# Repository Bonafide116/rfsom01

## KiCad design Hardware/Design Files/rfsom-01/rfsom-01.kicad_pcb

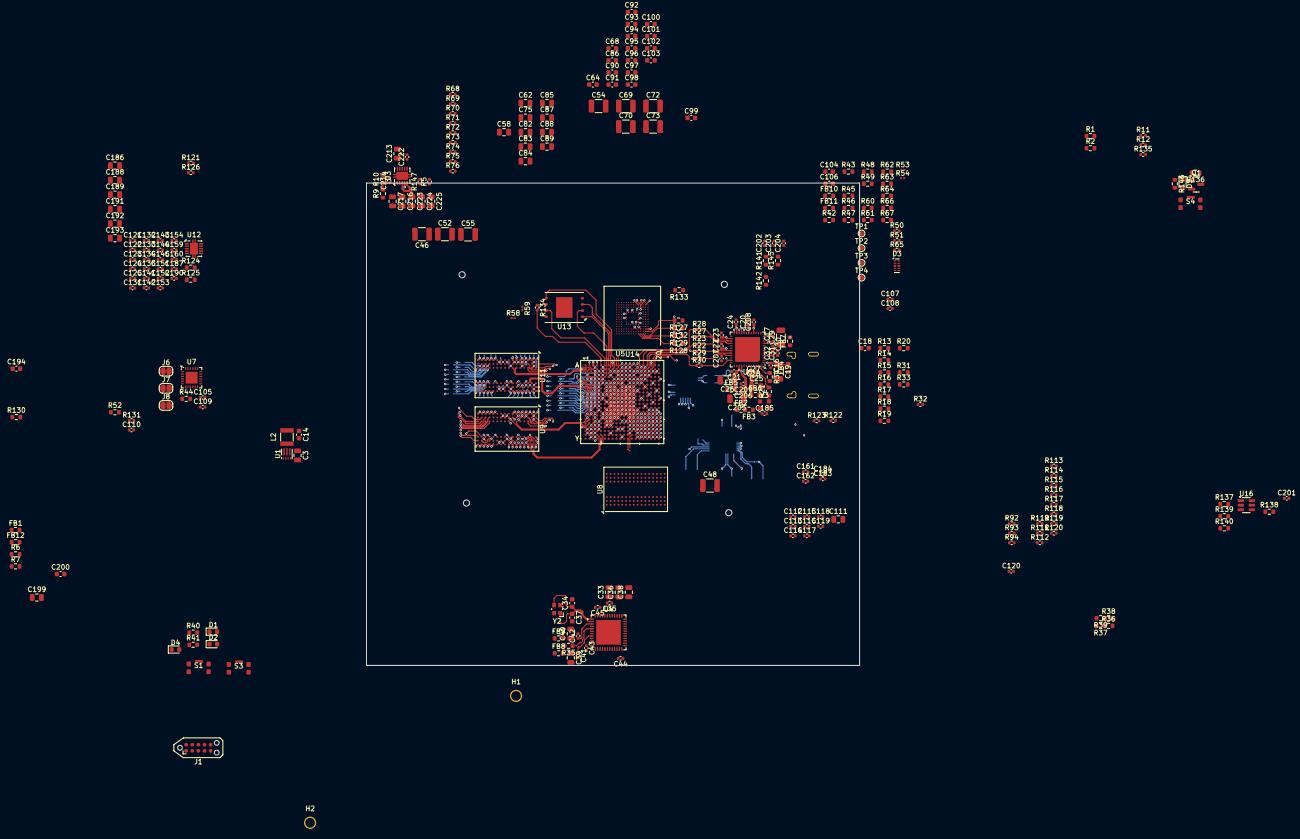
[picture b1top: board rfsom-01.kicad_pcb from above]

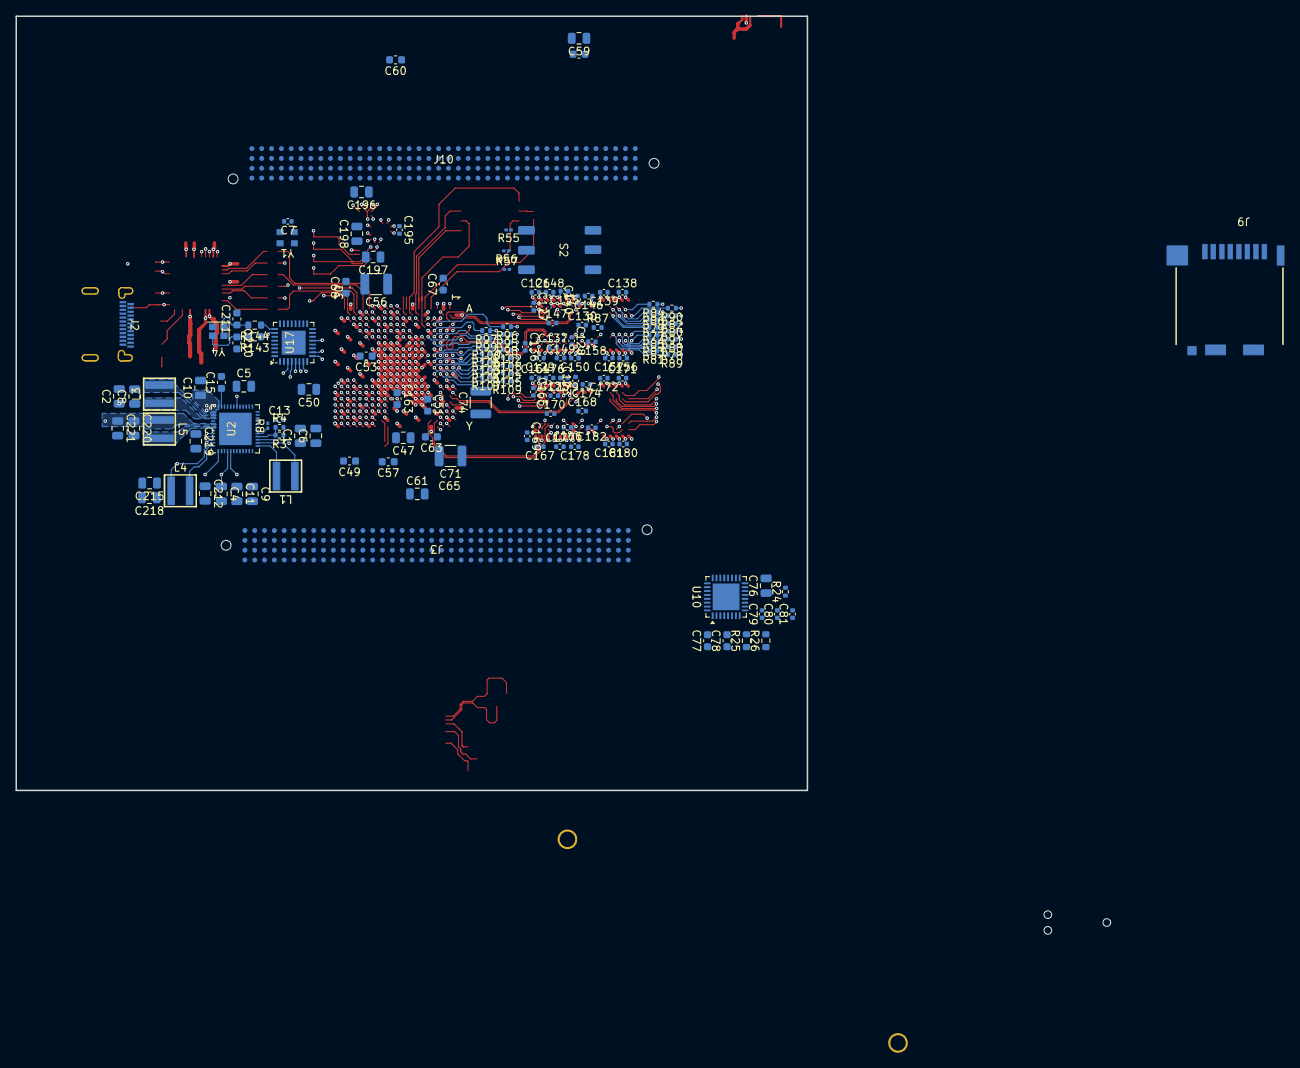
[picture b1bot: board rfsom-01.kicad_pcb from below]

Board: 10 copper layers, 102.2 x 100.0 mm, 432 parts (140 on the bottom side), 322 nets.

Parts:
C1, C8, C9, C10, C11, C47, C50, C58, C59, C61, C62, C75, C76, C82, C83, C84, C85, C87, C88, C89, C186, C212, C213, C218, C219, C221: CL21B475KPFNNNE; C_0805_2012Metric
C2, C4, C5, C6, C111, C188, C189, C191, C192, C193, C215, C216, C217, C220, C223, C224, C225: CL21B106KQQNFNE; C_0805_2012Metric
C3, C25, C33, C36, C38, C39, C40, C196, C197, C198, C199: CL21B475KAFNNNE; C_0805_2012Metric
C7, C13, C16, C17, C20, C21, C22, C23, C24, C27, C30, C31, C32, C35, C41, C42, C43, C44, C45, C79, C81, C105, C107, C108, C109, C110, C112, C113, C114, C115, C116, C117, C118, C119, C120, C185, C190, C195, C201, C202, C203, C204, C206, C207, C208, C209, C222: CL05B104KA5NNNC; C_0402_1005Metric
C14: GRM188R60G106ME47; C_0603_1608Metric
C15, C18, C77, C78, C104, C194, C200: CL10B105KA8NNNC; C_0603_1608Metric
C19, C26, C29, C205: CL31A106KBHNNNE; C_1206_3216Metric
C28, C80, C151, C160, C161, C162, C183, C184: CL05B103KB5NNNC; C_0402_1005Metric
C34, C37, C210, C211: CL10C060DB8NNNC; C_0603_1608Metric
C46, C48, C52, C55, C56, C73: GRM32EE70G107ME19K; C_1210_3225Metric
C49, C51, C53, C57, C60, C63, C64, C65, C66, C67, C68, C86, C90, C91, C92, C93, C94, C95, C96, C97, C98, C99, C100, C101, C102, C103, C106, C163: GRM188R70J474KA01D; C_0603_1608Metric
C54, C69, C70, C71, C72, C74: GRM32ER70J476ME20L; C_1210_3225Metric
C121, C122, C123, C124, C125, C126, C127, C128, C129, C130, C131, C132, C133, C134, C135, C136, C137, C138, C139, C140, C141, C142, C143, C144, C145, C146, C147, C148, C149, C150, C152, C153, C154, C155, C156, C157, C158, C159, C164, C165, C166, C167, C168, C169, C170, C171, C172, C173, C174, C175, C176, C177, C178, C179, C180, C181, C182: CL05B473KA5VPNC; C_0402_1005Metric
C187, C214: CL05B102KB5NNNC; C_0402_1005Metric
D1, D2, D4, D5: 150060BS75000; LED_0603_1608Metric
D3: ESD204DQAR; USON-10
FB1, FB2, FB3, FB4, FB5, FB6, FB7, FB8, FB9, FB10, FB11, FB12: MPZ1608S601ATA00; R_0603_1608Metric
H1, H2: MountingHole_Pad; MountingHole_2mm
J1: TC2050; Tag-Connect_TC2050-IDC-NL_2x05_P1.27mm_Vertical
J2: 2216100001
J3, J10: SEAM-40-02.0-L-04-2-A-K-TR; SEAM-40-XX.X-XXX-04-X-A-XX-XX
J6, J7, J8: SolderJumper-2_P1.3mm_Open_RoundedPad1.0x1.5mm
J9: DM3CS-SF
L1, L3, L4, L5: 74438357015; WE-MAPI
L2: DFE322512F-R47M=P2; IND_1210
Q1: BSS138; SOT-23
R1, R2, R9, R10, R13, R15, R17, R19, R25, R26, R63, R66, R67, R124, R125, R130, R133, R136, R137, R139, R140, R142: RC0603FR-0710KL; R_0603_1608Metric
R3: RC0402FR-13470KL; R_0402_1005Metric
R4, R5, R11, R12, R24, R126, R135, R147: RC0402FR-07100KL; R_0402_1005Metric
R6, R7: RC0603FR-135K11L; R_0603_1608Metric
R8, R53, R54, R55, R56, R57, R58, R59: RC0603FR-0720KL; R_0201_0603Metric
R14, R16, R18, R20, R31, R33, R60, R61, R62: RC0603FR-071KL; R_0603_1608Metric
R21: RC0603FR-0749R9L; R_0603_1608Metric
R22, R23, R27, R28, R29, R30, R95, R96, R97, R98, R99, R100, R101, R102, R103, R104, R105, R106, R107, R108, R109, R110, R111, R112, R113, R114, R115, R116, R117, R118, R131, R134: RC0402FR-0722RL; R_0402_1005Metric
R32, R50, R51, R92: RES_01; R_0402_1005Metric
R34: RC0603FR-076K04L; R_0603_1608Metric
R35: RES_01; R_0603_1608Metric
R36, R37, R38, R39, R42, R43: RC0603JR-070RL; R_0603_1608Metric
R40, R41, R49, R64, R146: RC0603FR-07220RL; R_0603_1608Metric
R44, R52, R127, R128, R129, R132: RC0603FR-0747K5L; R_0603_1608Metric
R45, R46, R47, R48, R143, R144: RC0402FR-07100RL; R_0603_1608Metric
R65, R68, R69, R70, R71, R72, R73, R74, R75, R76, R77, R78, R79, R80, R81, R82, R83, R84, R85, R86, R87, R88, R89, R90, R91, R93: RT0402FRE0740R2L; R_0402_1005Metric
R94, R119, R120: RC0402FR-0780R6L; R_0402_1005Metric
R121, R122, R123: RC0402FR-07240RL; R_0402_1005Metric
R138: RC0603FR-072KL; R_0603_1608Metric
R141: RC0603FR-078K06L; R_0603_1608Metric
R145: RC0603FR-071ML; R_0603_1608Metric
S1, S3, S4: 435441019830
S2: 219-3LPST
TP1, TP2, TP3, TP4: TestPoint_Pad_D1.0mm
U1: TPS62086RLT; RLT0007A
U2: TPS65218D0RSLT; RSL0048G
U3, U12: TPS51200DRCR; VSON-10-1EP_3x3mm_P0.5mm_EP1.65x2.4mm
U4: FT232HQ-REEL; QFN-48-1EP_7x7mm_P0.5mm_EP5.1x5.1mm
U5: XC7Z010-1CLG400C; CLG400
U6: KSZ9131RNXI-TR; MLPQ-48-1EP_7x7mm_P0.5mm
U7: TXS02612RTWR; QFN-24-1EP_4x4mm_P0.5mm
U8, U9, U11: AS4C256M16D3C-12BCN; BGA-96_9.0x13.0mm_Layout2x3x16_P0.8mm
U10: STM32L432KCUx; QFN-32-1EP_5x5mm_P0.5mm_EP3.45x3.45mm
U13: S25FL128SAGNFI003; PG-WSON-8_EP
U14: MX52LM04A11XSI; LFBGA-153_11.5x13mm_Layout14x14_P0.5mm
U16: 93LC56BT-I/OT; SOT-23-6
U17: USB3320C-EZK; QFN-32-1EP_5x5mm_P0.5mm
Y1: ECS-2033-500-BN; ECS-2033
Y2: ABM10-166-12.000MHZ-T3; Crystal_SMD_Abracon_ABM10-4Pin_2.5x2.0mm
Y3: ECS-2033-250-BN; ECS-2033
Y4: ECS-240-12-37B-CKY-TR; ECX-1637B

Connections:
+ETH_AVDDH: C16.1, C17.1, C19.1, FB4.2, U6.1 (AVDDH), U6.12 (AVDDH)
+ETH_AVDDL: C29.1, C30.1, C31.1, C32.1, FB7.1, U6.4 (AVDDL), U6.9 (AVDDL)
+ETH_DVDDH: C205.1, C206.1, C207.1, C208.1, C209.1, FB2.2, FB3.2, R33.2, U6.16 (DVDDH), U6.34 (DVDDH), U6.40 (DVDDH)
+ETH_DVDDL: C20.1, C21.1, C22.1, C23.1, C24.1, C26.1, FB5.2, U6.18 (DVDDL), U6.23 (DVDDL), U6.26 (DVDDL), U6.30 (DVDDL), U6.39 (DVDDL)
+LDO_3V3: C14.1, C76.1, C77.1, C78.1, C79.1, C80.1, C81.1, J1.1, L2.2, Q1.3 (D), R1.1, R2.1, R5.2, R11.1, R12.1, R25.1, R26.1, R135.1, R136.1, U1.3 (FB), U1.4 (VOS), U10.1 (VDD), U10.5 (VDDA), U10.17 (VDD)
+PL_VCC_1V5: C151.1, C188.1, C189.1, R124.1, U8.A1 (VDDQ), U8.A8 (VDDQ), U8.B2 (VDD), U8.C1 (VDDQ), U8.C9 (VDDQ), U8.D2 (VDDQ), U8.D9 (VDD), U8.E9 (VDDQ), U8.F1 (VDDQ), U8.G7 (VDD), U8.H2 (VDDQ), U8.H9 (VDDQ), U8.K2 (VDD), U8.K8 (VDD), U8.N1 (VDD), U8.N9 (VDD), U8.R1 (VDD), U8.R9 (VDD), U12.2 (VLDOIN)
+PL_VTT_0V75: C160.1, C191.1, C192.1, C193.1, U8.H1 (VREFDQ), U8.M8 (VREFCA), U12.3 (VO), U12.5 (VOSNS)
+PS_VCC_1V5: C216.1, C217.1, R9.1, R93.1, R120.2, U3.2 (VLDOIN)
+PS_VTT_0V75: C111.1, C112.1, C113.1, C114.1, C115.1, C116.1, C117.1, C118.1, C119.1, C120.1, C223.1, C224.1, C225.1, R68.1, R69.1, R70.1, R71.1, R72.1, R73.1, R74.1, R75.1, R76.1, R77.1, R78.1, R79.1, R80.1, R81.1, R82.1, R83.1, R84.1, R85.1, R86.1, R87.1, R88.1, R89.1, R90.1, R91.1, U3.3 (VO), U3.5 (VOSNS), U5.H6 (PS_DDR_VREF0_502), U5.P6 (PS_DDR_VREF1_502)
+PS_VTT_REF: C222.1, U3.6 (REFOUT), U12.6 (REFOUT)
+VCC_1V0: C48.1, C50.1, C53.1, C54.1, C58.1, C60.1, C64.1, C67.1, C73.1, C85.1, C90.1, C94.1, C215.1, C218.1, L4.1, U2.47 (FB1), U5.G7 (VCCPINT), U5.G11 (VCCBRAM), U5.G13 (VCCINT), U5.H10 (VCCBRAM), U5.H12 (VCCINT), U5.J7 (VCCPINT), U5.J13 (VCCINT), U5.K12 (VCCINT), U5.L7 (VCCPINT), U5.L13 (VCCINT), U5.M12 (VCCINT), U5.N7 (VCCPINT), U5.N13 (VCCINT), U5.P8 (VCCPINT), U5.P12 (VCCINT), U5.R7 (VCCPINT), U5.R13 (VCCINT)
+VCC_1V2: C220.1, C221.1, FB5.1, FB6.2, FB7.2, L5.1, U2.41 (FB2), U5.K10 (VREFN_0), U5.L9 (VREFP_0)
+VCC_1V5: C2.1, C8.1, C46.1, C47.1, C49.1, C51.1, C57.1, C63.1, C121.1, C122.1, C123.1, C124.1, C125.1, C126.1, C127.1, C128.1, C129.1, C130.1, C131.1, C132.1, C133.1, C134.1, C135.1, C136.1, C137.1, C138.1, C139.1, C140.1, C141.1, C142.1, C143.1, C144.1, C145.1, C146.1, C147.1, C148.1, C149.1, C150.1, C152.1, C153.1, C154.1, C155.1, C156.1, C157.1, C158.1, C159.1, C161.1, C164.1, C165.1, C166.1, C167.1, C168.1, C169.1, C170.1, C171.1, C172.1, C173.1, C174.1, C175.1, C176.1, C177.1, C178.1, C179.1, C180.1, C181.1, C182.1, C183.1, L3.1, U2.31 (IN_LS1), U2.39 (FB3), U5.A3 (VCCO_DDR_502), U5.D2 (VCCO_DDR_502), U5.E5 (VCCO_DDR_502), U5.G1 (VCCO_DDR_502), U5.H4 (VCCO_DDR_502), U5.L3 (VCCO_DDR_502), U5.P2 (VCCO_DDR_502), U5.R5 (VCCO_DDR_502), U5.U1 (VCCO_DDR_502), U5.V4 (VCCO_DDR_502), U9.A1 (VDDQ), U9.A8 (VDDQ), U9.B2 (VDD), U9.C1 (VDDQ), U9.C9 (VDDQ), U9.D2 (VDDQ), U9.D9 (VDD), U9.E9 (VDDQ), U9.F1 (VDDQ), U9.G7 (VDD), U9.H2 (VDDQ), U9.H9 (VDDQ), U9.K2 (VDD), U9.K8 (VDD), U9.N1 (VDD), U9.N9 (VDD), U9.R1 (VDD), U9.R9 (VDD), U11.A1 (VDDQ), U11.A8 (VDDQ), U11.B2 (VDD), U11.C1 (VDDQ), U11.C9 (VDDQ), U11.D2 (VDDQ), U11.D9 (VDD), U11.E9 (VDDQ), U11.F1 (VDDQ), U11.G7 (VDD), U11.H2 (VDDQ), U11.H9 (VDDQ), U11.K2 (VDD), U11.K8 (VDD), U11.N1 (VDD), U11.N9 (VDD), U11.R1 (VDD), U11.R9 (VDD)
+VCC_1V8: C4.1, C55.1, C56.1, C61.1, C62.1, C66.1, C68.1, C72.1, C84.1, C86.1, C104.1, C105.1, C163.1, C202.1, C203.1, C204.1, FB3.1, FB10.1, J6.2, R13.1, R15.1, R17.1, R19.1, R31.1, R52.1, R63.1, R66.1, R142.1, U2.4 (LDO1), U5.A13 (VCCO_MIO1_501), U5.B16 (VCCO_MIO1_501), U5.D12 (VCCO_MIO1_501), U5.E15 (VCCO_MIO1_501), U5.F8 (VCCPAUX), U5.G8 (VCCPLL), U5.G9 (VCCPAUX), U5.H8 (VCCPAUX), U5.J11 (VCCAUX), U5.K8 (VCCPAUX), U5.L11 (VCCAUX), U5.M8 (VCCPAUX), U5.N9 (VCCAUX), U5.N11 (VCCAUX), U5.P10 (VCCAUX), U5.R9 (VCCAUX), U7.5 (VCCA), U17.8 (REFSEL[0]), U17.11 (REFSEL[1]), U17.14 (REFSEL[2]), U17.28 (VDD18), U17.30 (VDD18), U17.32 (VDDIO)
+VCC_3V3: C1.1, C6.1, C7.1, C43.1, C44.1, C45.1, C52.1, C59.1, C65.1, C69.1, C70.1, C71.1, C74.1, C75.1, C82.1, C83.1, C87.1, C88.1, C89.1, C91.1, C92.1, C93.1, C95.1, C96.1, C97.1, C98.1, C99.1, C100.1, C101.1, C102.1, C103.1, C109.1, C110.1, C185.1, C186.1, C195.1, C196.1, C197.1, C198.1, C201.1, C213.1, D1.2 (A), D2.2 (A), FB2.1, FB4.1, FB8.1, FB9.1, J9.4 (VDD), R32.1, R50.2, R51.2, R53.1, R126.2, R127.1, R128.1, R129.1, R130.2, R132.1, R133.2, R137.1, R139.1, R140.1, R147.2, S2.4, S2.5, S2.6, U2.15 (DCDC4), U3.10 (VIN), U4.12 (VCCIO), U4.24 (VCCIO), U4.39 (VCCD), U4.46 (VCCIO), U5.B6 (VCCO_MIO0_500), U5.C19 (VCCO_35), U5.D7 (VCCO_MIO0_500), U5.F18 (VCCO_35), U5.H14 (VCCO_35), U5.J17 (VCCO_35), U5.K6 (VCCO_0), U5.K20 (VCCO_35), U5.M6 (CFGBVS_0), U5.M16 (VCCO_35), U5.N6 (RSVDVCC3), U5.N19 (VCCO_34), U5.R6 (RSVDVCC2), U5.R15 (VCCO_34), U5.T6 (RSVDVCC1), U5.T8 (VCCO_13), U5.T18 (VCCO_34), U5.U11 (VCCO_13), U5.V14 (VCCO_34), U5.W7 (VCCO_13), U5.W17 (VCCO_34), U5.Y10 (VCCO_13), U5.Y20 (VCCO_34), U7.17 (VCC_B1), U7.21 (VCC_B0), U12.10 (VIN), U13.8 (VCC), U14.C6 (VCCQ), U14.E6 (VCC), U14.F5 (VCC), U14.J10 (VCC), U14.K9 (VCC), U14.M4 (VCCQ), U14.N4 (VCCQ), U14.P3 (VCCQ), U14.P5 (VCCQ), U16.6 (VCC), U17.20 (VDD33), U17.21 (VBAT), Y1.1 (EN), Y1.4 (VDD), Y3.1 (EN), Y3.4 (VDD)
+VCC_DDR_1V5: C5.1, U2.30 (LS1)
+VIN_5V0: C3.1, C9.1, C10.1, C11.1, C33.1, C35.1, C212.1, C219.1, FB1.2, R3.1, U1.1 (EN), U1.7 (VIN), U2.1 (IN_DCDC1), U2.5 (IN_LDO1), U2.9 (AC_DET), U2.12 (IN_DCDC4), U2.27 (IN_BU), U2.36 (IN_BIAS), U2.37 (IN_DCDC3), U2.43 (IN_DCDC2), U4.40 (VREGIN)
+VTT_0V75: C162.1, C184.1, U9.H1 (VREFDQ), U9.M8 (VREFCA), U11.H1 (VREFDQ), U11.M8 (VREFCA)
+VUSB: C199.1, C200.1, FB1.1, J2.A4 (VBUS), J2.A9 (VBUS), J2.B4 (VBUS), J2.B9 (VBUS)
/TC_SWD_CLK: J1.5, U10.24 (PA14)
/TC_SWD_IO: J1.3, U10.23 (PA13)
/TC_USART_RX: J1.2, U10.8 (PA2)
/TC_USART_TX: J1.4, U10.25 (PA15)
/eth-phy/+ETH_1V2: C25.1, C27.1, C28.1, FB6.1, U6.44 (AVDDL_PLL)
/eth-phy/ENET0_MDC: U5.C10 (PS_MIO52_501), U6.36 (MDC)
/eth-phy/ENET0_RXCLK: R30.1, U5.B17 (PS_MIO22_501)
/eth-phy/ENET0_RXCLK_R: R30.2, U6.35 (RXC/PHYAD2)
/eth-phy/ENET0_RXCTL: R29.1, U5.D13 (PS_MIO27_501)
/eth-phy/ENET0_RXCTL_R: R29.2, U6.33 (RX_CTL/CLK125_EN)
/eth-phy/ENET0_RXD0: R22.1, U5.D11 (PS_MIO23_501)
/eth-phy/ENET0_RXD0_R: R13.2, R14.1, R22.2, U6.32 (RXD0/MODE0)
/eth-phy/ENET0_RXD1: R23.1, U5.A16 (PS_MIO24_501)
/eth-phy/ENET0_RXD1_R: R15.2, R16.1, R23.2, U6.31 (RXD1/MODE1)
/eth-phy/ENET0_RXD2: R27.1, U5.F15 (PS_MIO25_501)
/eth-phy/ENET0_RXD2_R: R17.2, R18.1, R27.2, U6.28 (RXD2/MODE2)
/eth-phy/ENET0_RXD3: R28.1, U5.A15 (PS_MIO26_501)
/eth-phy/ENET0_RXD3_R: R19.2, R20.1, R28.2, U6.27 (RXD3/MODE3)
/eth-phy/ENET0_TXCLK: U5.A19 (PS_MIO16_501), U6.24 (TXC)
/eth-phy/ENET0_TXCTL: U5.F14 (PS_MIO21_501), U6.25 (TX_CTL)
/eth-phy/ENET0_TXD0: U5.E14 (PS_MIO17_501), U6.19 (TXD0)
/eth-phy/ENET0_TXD1: U5.B18 (PS_MIO18_501), U6.20 (TXD1)
/eth-phy/ENET0_TXD2: U5.D10 (PS_MIO19_501), U6.21 (TXD2)
/eth-phy/ENET0_TXD3: U5.A17 (PS_MIO20_501), U6.22 (TXD3)
/eth-phy/ETH0_MDIO: R31.2, U5.C11 (PS_MIO53_501), U6.37 (MDIO)
/eth-phy/ETH_LED2: R33.1, U6.15 (LED2/PHYAD1)
/eth-phy/~ENET0_RST: C18.2, R32.2, U5.B13 (PS_MIO50_501), U6.42 (RESET_N)
/ftdi/FTDI_EECLK: R139.2, U4.44 (EECLK), U16.4 (CLK)
/ftdi/FTDI_EECS: R137.2, U4.45 (EECS), U16.5 (CS)
/ftdi/FTDI_EEDATA: R138.2, R140.2, U4.43 (EEDATA), U16.3 (DI)
/ftdi/FTDI_USB_D+: J2.A6 (D1+), J2.B6 (D2+), U4.6 (DM)
/ftdi/FTDI_USB_D-: J2.A7 (D1-), J2.B7 (D2-), U4.7 (DP)
/ftdi/RXLED: R40.1, U4.27 (ACBUS3)
/ftdi/TXLED: R41.1, U4.28 (ACBUS4)
/mcu/ST_I2C1_SCL: R2.2, R26.2, U2.3 (SCL), U10.29 (PB6)
/mcu/ST_I2C1_SDA: R1.2, R25.2, U2.2 (SDA), U10.30 (PB7)
/power/3V3_PGOOD: R5.1, U1.2 (PG)
/power/PMIC_PB: S4.2, S4.4, U2.44 (PB)
/power/PMIC_PGOOD: Q1.1 (G), R136.2, U2.8 (PGOOD)
/power/PMIC_nINT: R11.2, U2.45 (~INT)
/power/PMIC_nPFO: R135.2, U2.10 (~PFO)
/power/PMIC_nWKP: R12.2, U2.40 (~WAKEUP)
/power/PS_VTT_PGOOD: R147.1, U3.9 (PGOOD)
/soc/EMMC_CLK: R131.1, U5.D9 (PS_MIO12_500)
/soc/EMMC_CMD: R133.1, U5.C6 (PS_MIO11_500), U14.M5 (CMD)
/soc/EMMC_D0: R132.2, U5.E9 (PS_MIO10_500), U14.A3 (DAT0)
/soc/EMMC_D1: R129.2, U5.E8 (PS_MIO13_500), U14.A4 (DAT1)
/soc/EMMC_D2: R128.2, U5.C5 (PS_MIO14_500), U14.A5 (DAT2)
/soc/EMMC_D3: R127.2, U5.C8 (PS_MIO15_500), U14.B2 (DAT3)
/soc/FLSH_QSPI_IO0: R58.2, U5.B8 (PS_MIO2_500), U13.5 (SI/IO0)
/soc/FLSH_QSPI_IO1: R56.2, U5.D6 (PS_MIO3_500), U13.2 (SO/IO1)
/soc/FLSH_QSPI_IO2: R57.2, U5.B7 (PS_MIO4_500), U13.3 (~WP/IO2)
/soc/FLSH_QSPI_IO3: R55.2, U5.A6 (PS_MIO5_500), U13.7 (~HOLD/IO3)
/soc/FLSH_QSPI_SCK: R59.2, R134.2, U5.A5 (PS_MIO6_500)
/soc/FLSH_QSPI_nCS: U5.A7 (PS_MIO1_500), U13.1 (~CS)
/soc/SDC_CD: J7.2, J9.9 (CD), R52.2
/soc/SDC_CLK: J9.5 (CLK), U7.19 (CLK_B0)
/soc/SDC_CMD: J9.3 (CMD), U7.20 (CMD_B0)
/soc/SDC_DAT0: J9.7 (DAT0), U7.18 (DAT0_B0)
/soc/SDC_DAT1: J9.8 (DAT1), U7.16 (DAT1_B0)
/soc/SDC_DAT2: J9.1 (DAT2), U7.23 (DAT2_B0)
/soc/SDC_DAT3: J9.2 (DAT3), U7.22 (DAT3_B0)
/soc/SD_CLK: R65.2, U7.9 (CLKA)
/soc/SD_CMD: U5.C17 (PS_MIO41_501), U7.4 (CMDA)
/soc/SD_D0: U5.E12 (PS_MIO42_501), U7.6 (DAT0A)
/soc/SD_D1: U5.A9 (PS_MIO43_501), U7.7 (DAT1A)
/soc/SD_D2: U5.F13 (PS_MIO44_501), U7.1 (DAT2A)
/soc/SD_D3: U5.B15 (PS_MIO45_501), U7.3 (DAT3A)
/soc/SD_SEL: J6.1, R44.1, U7.24 (SEL)
/soc/soc-pl/DDR3_ADDR0: U5.P14 (IO_L6P_T0_34), U8.N3 (A0)
/soc/soc-pl/DDR3_ADDR1: U5.R14 (IO_L6N_T0_VREF_34), U8.P7 (A1)
/soc/soc-pl/DDR3_ADDR2: U5.Y16 (IO_L7P_T1_34), U8.P3 (A2)
/soc/soc-pl/DDR3_ADDR3: U5.Y17 (IO_L7N_T1_34), U8.N2 (A3)
/soc/soc-pl/DDR3_ADDR4: U5.W14 (IO_L8P_T1_34), U8.P8 (A4)
/soc/soc-pl/DDR3_ADDR5: U5.Y14 (IO_L8N_T1_34), U8.P2 (A5)
/soc/soc-pl/DDR3_ADDR6: U5.T16 (IO_L9P_T1_DQS_34), U8.R8 (A6)
/soc/soc-pl/DDR3_ADDR7: U5.U17 (IO_L9N_T1_DQS_34), U8.R2 (A7)
/soc/soc-pl/DDR3_ADDR8: U5.V15 (IO_L10P_T1_34), U8.T8 (A8)
/soc/soc-pl/DDR3_ADDR9: U5.W15 (IO_L10N_T1_34), U8.R3 (A9)
/soc/soc-pl/DDR3_ADDR10: U5.U14 (IO_L11P_T1_SRCC_34), U8.L7 (A10/AP)
/soc/soc-pl/DDR3_ADDR11: U5.U15 (IO_L11N_T1_SRCC_34), U8.R7 (A11)
/soc/soc-pl/DDR3_ADDR12: U5.U18 (IO_L12P_T1_MRCC_34), U8.N7 (A12/~BC)
/soc/soc-pl/DDR3_ADDR13: U5.U19 (IO_L12N_T1_MRCC_34), U8.T3 (A13)
/soc/soc-pl/DDR3_ADDR14: U5.N18 (IO_L13P_T2_MRCC_34), U8.T7 (A14)
/soc/soc-pl/DDR3_BA0: U5.U20 (IO_L15N_T2_DQS_34), U8.M2 (BA0)
/soc/soc-pl/DDR3_BA1: U5.N20 (IO_L14P_T2_SRCC_34), U8.N8 (BA1)
/soc/soc-pl/DDR3_BA2: U5.P20 (IO_L14N_T2_SRCC_34), U8.M3 (BA2)
/soc/soc-pl/DDR3_CK+: U5.V20 (IO_L16P_T2_34), U8.J7 (CK)
/soc/soc-pl/DDR3_CK-: U5.W20 (IO_L16N_T2_34), U8.K7 (~CK)
/soc/soc-pl/DDR3_CKE: U5.R16 (IO_L19P_T3_34), U8.K9 (CKE)
/soc/soc-pl/DDR3_D0: U5.R19 (IO_0_34), U8.E3 (DQ0)
/soc/soc-pl/DDR3_D1: U5.T11 (IO_L1P_T0_34), U8.F7 (DQ1)
/soc/soc-pl/DDR3_D2: U5.T10 (IO_L1N_T0_34), U8.F2 (DQ2)
/soc/soc-pl/DDR3_D3: U5.T12 (IO_L2P_T0_34), U8.F8 (DQ3)
/soc/soc-pl/DDR3_D4: U5.U12 (IO_L2N_T0_34), U8.H3 (DQ4)
/soc/soc-pl/DDR3_D5: U5.P19 (IO_L13N_T2_MRCC_34), U8.H8 (DQ5)
/soc/soc-pl/DDR3_D6: U5.T20 (IO_L15P_T2_DQS_34), U8.G2 (DQ6)
/soc/soc-pl/DDR3_D7: U5.R17 (IO_L19N_T3_VREF_34), U8.H7 (DQ7)
/soc/soc-pl/DDR3_D8: U5.V17 (IO_L21P_T3_DQS_34), U8.D7 (DQ8)
/soc/soc-pl/DDR3_D9: U5.V18 (IO_L21N_T3_DQS_34), U8.C3 (DQ9)
/soc/soc-pl/DDR3_D10: U5.W18 (IO_L22P_T3_34), U8.C8 (DQ10)
/soc/soc-pl/DDR3_D11: U5.W19 (IO_L22N_T3_34), U8.C2 (DQ11)
/soc/soc-pl/DDR3_D12: U5.N17 (IO_L23P_T3_34), U8.A7 (DQ12)
/soc/soc-pl/DDR3_D13: U5.P18 (IO_L23N_T3_34), U8.A2 (DQ13)
/soc/soc-pl/DDR3_D14: U5.P15 (IO_L24P_T3_34), U8.B8 (DQ14)
/soc/soc-pl/DDR3_D15: U5.P16 (IO_L24N_T3_34), U8.A3 (DQ15)
/soc/soc-pl/DDR3_DM0: U5.T14 (IO_L5P_T0_34), U8.E7 (LDM)
/soc/soc-pl/DDR3_DM1: U5.T15 (IO_L5N_T0_34), U8.D3 (UDM)
/soc/soc-pl/DDR3_DQS0+: U5.U13 (IO_L3P_T0_DQS_PUDC_B_34), U8.F3 (LDQS)
/soc/soc-pl/DDR3_DQS0-: U5.V13 (IO_L3N_T0_DQS_34), U8.G3 (~LDQS)
/soc/soc-pl/DDR3_DQS1+: U5.V12 (IO_L4P_T0_34), U8.C7 (UDQS)
/soc/soc-pl/DDR3_DQS1-: U5.W13 (IO_L4N_T0_34), U8.B7 (~UDQS)
/soc/soc-pl/DDR3_ODT0: U5.R18 (IO_L20N_T3_34), U8.K1 (ODT)
/soc/soc-pl/DDR3_nCAS: U5.Y19 (IO_L17N_T2_34), U8.K3 (~CAS)
/soc/soc-pl/DDR3_nCS: U5.T17 (IO_L20P_T3_34), U8.L2 (~CS)
/soc/soc-pl/DDR3_nRAS: U5.Y18 (IO_L17P_T2_34), U8.J3 (~RAS)
/soc/soc-pl/DDR3_nRST: U5.W16 (IO_L18N_T2_34), U8.T2 (~RESET)
/soc/soc-pl/DDR3_nWE: U5.V16 (IO_L18P_T2_34), U8.L3 (~WE)
/soc/soc-pl/ram-pl/PL_VTT_PGOOD: R126.1, U12.9 (PGOOD)
/soc/soc-ps/JTAG_TCK: D3.4 (IO3), D3.7 (NC), R47.1, TP3.1
/soc/soc-ps/JTAG_TCK_R: R36.2, R47.2, U5.F9 (TCK_0)
/soc/soc-ps/JTAG_TDI: D3.2 (IO2), D3.9 (NC), R46.1, TP2.1
/soc/soc-ps/JTAG_TDI_R: R38.2, R46.2, U5.G6 (TDI_0)
/soc/soc-ps/JTAG_TDO: D3.1 (IO1), D3.10 (NC), R45.1, TP1.1
/soc/soc-ps/JTAG_TDO_R: R45.2, U4.15 (ADBUS2), U5.F6 (TDO_0)
/soc/soc-ps/JTAG_TMS: D3.5 (IO4), D3.6 (NC), R48.1, TP4.1
/soc/soc-ps/JTAG_TMS_R: R48.2, U4.16 (ADBUS3), U5.J6 (TMS_0)
/soc/soc-ps/MIO7: R54.2, U5.D8 (PS_MIO7_500)
/soc/soc-ps/MIO8: R53.2, U5.D5 (PS_MIO8_500)
/soc/soc-ps/PS_CLK_50M: U5.E7 (PS_CLK_500), Y1.3 (OUT)
/soc/soc-ps/RGMII_VREF: R66.2, R67.1, U5.E11 (PS_MIO_VREF_501)
/soc/soc-ps/SD0_CD: J7.1, J8.2, U5.B12 (PS_MIO48_501)
/soc/soc-ps/USB0_CLK: R143.1, U5.A11 (PS_MIO36_501), U17.26 (REFCLK)
/soc/soc-ps/USB0_DATA0: U5.A14 (PS_MIO32_501), U17.3 (DATA[0])
/soc/soc-ps/USB0_DATA1: U5.D15 (PS_MIO33_501), U17.4 (DATA[1])
/soc/soc-ps/USB0_DATA2: U5.A12 (PS_MIO34_501), U17.5 (DATA[2])
/soc/soc-ps/USB0_DATA3: U5.F12 (PS_MIO35_501), U17.6 (DATA[3])
/soc/soc-ps/USB0_DATA4: U5.C16 (PS_MIO28_501), U17.7 (DATA[4])
/soc/soc-ps/USB0_DATA5: U5.A10 (PS_MIO37_501), U17.9 (DATA[5])
/soc/soc-ps/USB0_DATA6: U5.E13 (PS_MIO38_501), U17.10 (DATA[6])
/soc/soc-ps/USB0_DATA7: U5.C18 (PS_MIO39_501), U17.13 (DATA[7])
/soc/soc-ps/USB0_DIR: U5.C13 (PS_MIO29_501), U17.31 (DIR)
/soc/soc-ps/USB0_NXT: U5.E16 (PS_MIO31_501), U17.2 (NXT)
/soc/soc-ps/USB0_STP: U5.C15 (PS_MIO30_501), U17.29 (STP)
/soc/soc-ps/VADC+: C106.1, C107.1, C108.1, FB10.2, R42.2, U5.J9 (VCCADC_0), U5.K9 (VP_0)
/soc/soc-ps/VADC-: C106.2, C107.2, C108.2, FB11.2, R43.2, U5.J10 (GNDADC_0), U5.L10 (VN_0)
/soc/soc-ps/ZYNQ_DONE_0: D4.2 (A), U5.R11 (DONE_0)
/soc/soc-ps/ZYNQ_NRST: R63.2, R64.1, U5.B10 (PS_SRST_B_501)
/soc/soc-ps/~USB_RST: R142.2, U5.B9 (PS_MIO51_501), U17.27 (~RESET)
/soc/soc-ram/DDR3_A0: R109.2, U5.N2 (PS_DDR_A0_502)
/soc/soc-ram/DDR3_A1: R108.2, U5.K2 (PS_DDR_A1_502)
/soc/soc-ram/DDR3_A2: R107.2, U5.M3 (PS_DDR_A2_502)
/soc/soc-ram/DDR3_A3: R106.2, U5.K3 (PS_DDR_A3_502)
/soc/soc-ram/DDR3_A4: R105.2, U5.M4 (PS_DDR_A4_502)
/soc/soc-ram/DDR3_A5: R104.2, U5.L1 (PS_DDR_A5_502)
/soc/soc-ram/DDR3_A6: R103.2, U5.L4 (PS_DDR_A6_502)
/soc/soc-ram/DDR3_A7: R102.2, U5.K4 (PS_DDR_A7_502)
/soc/soc-ram/DDR3_A8: R101.2, U5.K1 (PS_DDR_A8_502)
/soc/soc-ram/DDR3_A9: R100.2, U5.J4 (PS_DDR_A9_502)
/soc/soc-ram/DDR3_A10: R99.2, U5.F5 (PS_DDR_A10_502)
/soc/soc-ram/DDR3_A11: R98.2, U5.G4 (PS_DDR_A11_502)
/soc/soc-ram/DDR3_A12: R97.2, U5.E4 (PS_DDR_A12_502)
/soc/soc-ram/DDR3_A13: R96.2, U5.D4 (PS_DDR_A13_502)
/soc/soc-ram/DDR3_A14: R95.2, U5.F4 (PS_DDR_A14_502)
/soc/soc-ram/DDR3_ADDR0: R77.2, R109.1, U9.N3 (A0), U11.N3 (A0)
/soc/soc-ram/DDR3_ADDR1: R78.2, R108.1, U9.P7 (A1), U11.P7 (A1)
/soc/soc-ram/DDR3_ADDR2: R79.2, R107.1, U9.P3 (A2), U11.P3 (A2)
/soc/soc-ram/DDR3_ADDR3: R80.2, R106.1, U9.N2 (A3), U11.N2 (A3)
/soc/soc-ram/DDR3_ADDR4: R81.2, R105.1, U9.P8 (A4), U11.P8 (A4)
/soc/soc-ram/DDR3_ADDR5: R82.2, R104.1, U9.P2 (A5), U11.P2 (A5)
/soc/soc-ram/DDR3_ADDR6: R83.2, R103.1, U9.R8 (A6), U11.R8 (A6)
/soc/soc-ram/DDR3_ADDR7: R84.2, R102.1, U9.R2 (A7), U11.R2 (A7)
/soc/soc-ram/DDR3_ADDR8: R85.2, R101.1, U9.T8 (A8), U11.T8 (A8)
/soc/soc-ram/DDR3_ADDR9: R86.2, R100.1, U9.R3 (A9), U11.R3 (A9)
/soc/soc-ram/DDR3_ADDR10: R87.2, R99.1, U9.L7 (A10/AP), U11.L7 (A10/AP)
/soc/soc-ram/DDR3_ADDR11: R88.2, R98.1, U9.R7 (A11), U11.R7 (A11)
/soc/soc-ram/DDR3_ADDR12: R89.2, R97.1, U9.N7 (A12/~BC), U11.N7 (A12/~BC)
/soc/soc-ram/DDR3_ADDR13: R90.2, R96.1, U9.T3 (A13), U11.T3 (A13)
/soc/soc-ram/DDR3_ADDR14: R91.2, R95.1, U9.T7 (A14), U11.T7 (A14)
/soc/soc-ram/DDR3_BA0: R76.2, R112.1, U9.M2 (BA0), U11.M2 (BA0)
/soc/soc-ram/DDR3_BA1: R75.2, R111.1, U9.N8 (BA1), U11.N8 (BA1)
/soc/soc-ram/DDR3_BA2: R74.2, R110.1, U9.M3 (BA2), U11.M3 (BA2)
/soc/soc-ram/DDR3_CK+: R119.1, U5.L2 (PS_DDR_CKP_502), U9.J7 (CK), U11.J7 (CK)
/soc/soc-ram/DDR3_CK-: R119.2, U5.M2 (PS_DDR_CKN_502), U9.K7 (~CK), U11.K7 (~CK)
/soc/soc-ram/DDR3_CKE: R73.2, R93.2, R117.1, U9.K9 (CKE), U11.K9 (CKE)
/soc/soc-ram/DDR3_D0: U5.B3 (PS_DDR_DQ1_502), U11.E3 (DQ0)
/soc/soc-ram/DDR3_D1: U5.D1 (PS_DDR_DQ5_502), U11.F7 (DQ1)
/soc/soc-ram/DDR3_D2: U5.A2 (PS_DDR_DQ2_502), U11.F2 (DQ2)
/soc/soc-ram/DDR3_D3: U5.E1 (PS_DDR_DQ7_502), U11.F8 (DQ3)
/soc/soc-ram/DDR3_D4: U5.C3 (PS_DDR_DQ0_502), U11.H3 (DQ4)
/soc/soc-ram/DDR3_D5: U5.C1 (PS_DDR_DQ6_502), U11.H8 (DQ5)
/soc/soc-ram/DDR3_D6: U5.A4 (PS_DDR_DQ3_502), U11.G2 (DQ6)
/soc/soc-ram/DDR3_D7: U5.D3 (PS_DDR_DQ4_502), U11.H7 (DQ7)
/soc/soc-ram/DDR3_D8: U5.H2 (PS_DDR_DQ13_502), U11.D7 (DQ8)
/soc/soc-ram/DDR3_D9: U5.H3 (PS_DDR_DQ11_502), U11.C3 (DQ9)
/soc/soc-ram/DDR3_D10: U5.J1 (PS_DDR_DQ15_502), U11.C8 (DQ10)
/soc/soc-ram/DDR3_D11: U5.G3 (PS_DDR_DQ10_502), U11.C2 (DQ11)
/soc/soc-ram/DDR3_D12: U5.J3 (PS_DDR_DQ12_502), U11.A7 (DQ12)
/soc/soc-ram/DDR3_D13: U5.E3 (PS_DDR_DQ9_502), U11.A2 (DQ13)
/soc/soc-ram/DDR3_D14: U5.H1 (PS_DDR_DQ14_502), U11.B8 (DQ14)
/soc/soc-ram/DDR3_D15: U5.E2 (PS_DDR_DQ8_502), U11.A3 (DQ15)
/soc/soc-ram/DDR3_D16: U5.R1 (PS_DDR_DQ19_502), U9.E3 (DQ0)
/soc/soc-ram/DDR3_D17: U5.U2 (PS_DDR_DQ22_502), U9.F7 (DQ1)
/soc/soc-ram/DDR3_D18: U5.P1 (PS_DDR_DQ16_502), U9.F2 (DQ2)
/soc/soc-ram/DDR3_D19: U5.U3 (PS_DDR_DQ23_502), U9.F8 (DQ3)
/soc/soc-ram/DDR3_D20: U5.P3 (PS_DDR_DQ17_502), U9.H3 (DQ4)
/soc/soc-ram/DDR3_D21: U5.U4 (PS_DDR_DQ21_502), U9.H8 (DQ5)
/soc/soc-ram/DDR3_D22: U5.R3 (PS_DDR_DQ18_502), U9.G2 (DQ6)
/soc/soc-ram/DDR3_D23: U5.T4 (PS_DDR_DQ20_502), U9.H7 (DQ7)
/soc/soc-ram/DDR3_D24: U5.Y3 (PS_DDR_DQ25_502), U9.D7 (DQ8)
/soc/soc-ram/DDR3_D25: U5.V3 (PS_DDR_DQ31_502), U9.C3 (DQ9)
/soc/soc-ram/DDR3_D26: U5.Y4 (PS_DDR_DQ27_502), U9.C8 (DQ10)
/soc/soc-ram/DDR3_D27: U5.W1 (PS_DDR_DQ26_502), U9.C2 (DQ11)
/soc/soc-ram/DDR3_D28: U5.W3 (PS_DDR_DQ29_502), U9.A7 (DQ12)
/soc/soc-ram/DDR3_D29: U5.V1 (PS_DDR_DQ24_502), U9.A2 (DQ13)
/soc/soc-ram/DDR3_D30: U5.Y2 (PS_DDR_DQ28_502), U9.B8 (DQ14)
/soc/soc-ram/DDR3_D31: U5.V2 (PS_DDR_DQ30_502), U9.A3 (DQ15)
/soc/soc-ram/DDR3_DM0: U5.A1 (PS_DDR_DM0_502), U11.E7 (LDM)
/soc/soc-ram/DDR3_DM1: U5.F1 (PS_DDR_DM1_502), U11.D3 (UDM)
/soc/soc-ram/DDR3_DM2: U5.T1 (PS_DDR_DM2_502), U9.E7 (LDM)
/soc/soc-ram/DDR3_DM3: U5.Y1 (PS_DDR_DM3_502), U9.D3 (UDM)
/soc/soc-ram/DDR3_DQS0+: U5.C2 (PS_DDR_DQS_P0_502), U11.F3 (LDQS)
/soc/soc-ram/DDR3_DQS0-: U5.B2 (PS_DDR_DQS_N0_502), U11.G3 (~LDQS)
/soc/soc-ram/DDR3_DQS1+: U5.G2 (PS_DDR_DQS_P1_502), U11.C7 (UDQS)
/soc/soc-ram/DDR3_DQS1-: U5.F2 (PS_DDR_DQS_N1_502), U11.B7 (~UDQS)
/soc/soc-ram/DDR3_DQS2+: U5.R2 (PS_DDR_DQS_P2_502), U9.F3 (LDQS)
/soc/soc-ram/DDR3_DQS2-: U5.T2 (PS_DDR_DQS_N2_502), U9.G3 (~LDQS)
/soc/soc-ram/DDR3_DQS3+: U5.W5 (PS_DDR_DQS_P3_502), U9.C7 (UDQS)
/soc/soc-ram/DDR3_DQS3-: U5.W4 (PS_DDR_DQS_N3_502), U9.B7 (~UDQS)
/soc/soc-ram/DDR3_ODT0: R68.2, R118.1, U9.K1 (ODT), U11.K1 (ODT)
/soc/soc-ram/DDR3_RST: R92.1, U5.B4 (PS_DDR_DRST_B_502)
/soc/soc-ram/DDR3_nCAS: R70.2, R114.1, U9.K3 (~CAS), U11.K3 (~CAS)
/soc/soc-ram/DDR3_nCS: R72.2, R115.1, U9.L2 (~CS), U11.L2 (~CS)
/soc/soc-ram/DDR3_nRAS: R71.2, R113.1, U9.J3 (~RAS), U11.J3 (~RAS)
/soc/soc-ram/DDR3_nRST: U9.T2 (~RESET), U11.T2 (~RESET)
/soc/soc-ram/DDR3_nWE: R69.2, R116.1, U9.L3 (~WE), U11.L3 (~WE)
/soc/~EMMC_RST: R130.1, U14.K5 (~RST)
/~TC_SWD_RST: J1.7, R24.1, U10.4 (NRST)
GND: C1.2, C2.2, C3.2, C4.2, C5.2, C6.2, C7.2, C8.2, C9.2, C10.2, C11.2, C13.2, C14.2, C15.2, C16.2, C17.2, C18.1, C19.2, C20.2, C21.2, C22.2, C23.2, C24.2, C25.2, C26.2, C27.2, C28.2, C29.2, C30.2, C31.2, C32.2, C33.2, C34.2, C35.2, C36.2, C37.2, C38.2, C39.2, C40.2, C41.2, C42.2, C43.2, C44.2, C45.2, C46.2, C47.2, C48.2, C49.2, C50.2, C51.2, C52.2, C53.2, C54.2, C55.2, C56.2, C57.2, C58.2, C59.2, C60.2, C61.2, C62.2, C63.2, C64.2, C65.2, C66.2, C67.2, C68.2, C69.2, C70.2, C71.2, C72.2, C73.2, C74.2, C75.2, C76.2, C77.2, C78.2, C79.2, C80.2, C81.2, C82.2, C83.2, C84.2, C85.2, C86.2, C87.2, C88.2, C89.2, C90.2, C91.2, C92.2, C93.2, C94.2, C95.2, C96.2, C97.2, C98.2, C99.2, C100.2, C101.2, C102.2, C103.2, C104.2, C105.2, C109.2, C110.2, C111.2, C112.2, C113.2, C114.2, C115.2, C116.2, C117.2, C118.2, C119.2, C120.2, C121.2, C122.2, C123.2, C124.2, C125.2, C126.2, C127.2, C128.2, C129.2, C130.2, C131.2, C132.2, C133.2, C134.2, C135.2, C136.2, C137.2, C138.2, C139.2, C140.2, C141.2, C142.2, C143.2, C144.2, C145.2, C146.2, C147.2, C148.2, C149.2, C150.2, C151.2, C152.2, C153.2, C154.2, C155.2, C156.2, C157.2, C158.2, C159.2, C160.2, C161.2, C162.2, C163.2, C164.2, C165.2, C166.2, C167.2, C168.2, C169.2, C170.2, C171.2, C172.2, C173.2, C174.2, C175.2, C176.2, C177.2, C178.2, C179.2, C180.2, C181.2, C182.2, C183.2, C184.2, C185.2, C186.2, C187.2, C188.2, C189.2, C190.2, C191.2, C192.2, C193.2, C194.2, C195.2, C196.2, C197.2, C198.2, C201.2, C202.2, C203.2, C204.2, C205.2, C206.2, C207.2, C208.2, C209.2, C210.2, C211.2, C212.2, C213.2, C214.2, C215.2, C216.2, C217.2, C218.2, C219.2, C220.2, C221.2, C222.2, C223.2, C224.2, C225.2, D3.3 (GND), D3.8 (GND), FB11.1, FB12.2, H1.1, H2.1, J1.9, J9.6 (VSS), J9.S1, J9.S2, J9.S3, J9.S4, R4.2, R8.2, R10.2, R14.2, R16.2, R18.2, R20.2, R24.2, R34.2, R35.2, R44.2, R49.1, R54.1, R58.1, R59.1, R60.2, R61.2, R62.2, R67.2, R92.2, R94.2, R121.2, R122.2, R123.2, R125.2, R141.2, R146.2, S1.2, S1.4, S3.2, S3.4, S4.1, S4.3, U1.5 (GND), U2.20 (L5), U2.21 (FB5), U2.22 (FB6), U2.23 (L6), U2.24 (SYS_BU), U2.49 (EP), U3.4 (PGND), U3.8 (GND), U3.11 (EP), U4.4 (AGND), U4.9 (AGND), U4.10 (GND), U4.11 (GND), U4.22 (GND), U4.23 (GND), U4.35 (GND), U4.36 (GND), U4.41 (AGND), U4.42 (TEST), U4.47 (GND), U4.48 (GND), U5.A8 (GND), U5.A18 (GND), U5.B1 (GND), U5.B11 (GND), U5.C4 (GND), U5.C9 (GND), U5.C14 (GND), U5.D17 (GND), U5.E10 (GND), U5.E20 (GND), U5.F3 (GND), U5.F7 (GND), U5.F10 (RSVDGND), U5.G10 (GND), U5.G12 (GND), U5.G16 (GND), U5.H7 (GND), U5.H9 (GND), U5.H11 (GND), U5.H13 (GND), U5.H19 (GND), U5.J2 (GND), U5.J8 (GND), U5.J12 (GND), U5.K5 (GND), U5.K7 (GND), U5.K11 (GND), U5.K13 (GND), U5.K15 (GND), U5.L8 (GND), U5.L12 (GND), U5.L18 (GND), U5.M1 (GND), U5.M7 (GND), U5.M9 (DXP_0), U5.M10 (DXN_0), U5.M11 (GND), U5.M13 (GND), U5.N4 (GND), U5.N8 (GND), U5.N10 (GND), U5.N12 (GND), U5.N14 (GND), U5.P7 (GND), U5.P9 (GND), U5.P11 (GND), U5.P13 (GND), U5.P17 (GND), U5.R8 (GND), U5.R12 (GND), U5.R20 (GND), U5.T3 (GND), U5.T7 (GND), U5.T13 (GND), U5.U6 (GND), U5.U16 (GND), U5.V9 (GND), U5.V19 (GND), U5.W2 (GND), U5.W12 (GND), U5.Y5 (GND), U5.Y15 (GND), U6.29 (VSS), U6.45 (XO), U6.49 (EP), U7.2 (GND), U7.11 (GND), U7.25 (EP), U8.A9 (VSS), U8.B1 (VSSQ), U8.B3 (VSS), U8.B9 (VSSQ), U8.D1 (VSSQ), U8.D8 (VSSQ), U8.E1 (VSS), U8.E2 (VSSQ), U8.E8 (VSSQ), U8.F9 (VSSQ), U8.G1 (VSSQ), U8.G8 (VSS), U8.G9 (VSSQ), U8.J2 (VSS), U8.J8 (VSS), U8.M1 (VSS), U8.M9 (VSS), U8.P1 (VSS), U8.P9 (VSS), U8.T1 (VSS), U8.T9 (VSS), U9.A9 (VSS), U9.B1 (VSSQ), U9.B3 (VSS), U9.B9 (VSSQ), U9.D1 (VSSQ), U9.D8 (VSSQ), U9.E1 (VSS), U9.E2 (VSSQ), U9.E8 (VSSQ), U9.F9 (VSSQ), U9.G1 (VSSQ), U9.G8 (VSS), U9.G9 (VSSQ), U9.J2 (VSS), U9.J8 (VSS), U9.M1 (VSS), U9.M9 (VSS), U9.P1 (VSS), U9.P9 (VSS), U9.T1 (VSS), U9.T9 (VSS), U10.16 (VSS), U10.32 (VSS), U10.33 (VSS), U11.A9 (VSS), U11.B1 (VSSQ), U11.B3 (VSS), U11.B9 (VSSQ), U11.D1 (VSSQ), U11.D8 (VSSQ), U11.E1 (VSS), U11.E2 (VSSQ), U11.E8 (VSSQ), U11.F9 (VSSQ), U11.G1 (VSSQ), U11.G8 (VSS), U11.G9 (VSSQ), U11.J2 (VSS), U11.J8 (VSS), U11.M1 (VSS), U11.M9 (VSS), U11.P1 (VSS), U11.P9 (VSS), U11.T1 (VSS), U11.T9 (VSS), U12.4 (PGND), U12.8 (GND), U12.11 (EP), U13.4 (VSS), U13.9 (EP), U14.A6 (VSS), U14.C4 (VSSQ), U14.E7 (VSS), U14.G5 (VSS), U14.H10 (VSS), U14.J5 (VSS), U14.K8 (VSS), U14.N2 (VSSQ), U14.N5 (VCCQ), U14.P4 (VSSQ), U14.P6 (VSSQ), U16.2 (VSS), Y1.2 (GND), Y2.2, Y2.4, Y3.2 (GND), Y4.2, Y4.4
GND_USB: C199.2, C200.2, FB12.1, J2.A1 (GND), J2.A12 (GND), J2.B1 (GND), J2.B12 (GND), J2.SH1 (SHIELD1), J2.SH2 (SHIELD2), R6.2, R7.2
unnamed: C210.1, R143.2, R145.1, Y4.3
unnamed: C211.1, R144.2, R145.2, Y4.1
unnamed: D1.1 (K), R40.2
unnamed: D2.1 (K), R41.2
unnamed: D4.1 (K), R49.2
unnamed: D5.2 (A), Q1.2 (S)
unnamed: D5.1 (K), R146.1
unnamed: J2.A5 (CC1), R6.1
unnamed: J2.B5 (CC2), R7.1
unnamed: R55.1, R60.1, S2.1
unnamed: R56.1, R61.1, S2.2
unnamed: R57.1, R62.1, S2.3
unnamed: R64.2, S3.1, S3.3
unnamed: L2.1, U1.6 (SW)
unnamed: R8.1, U2.17 (DC34_SEL)
unnamed: C15.1, U2.35 (INT_LDO)
unnamed: L4.2, U2.48 (L1)
unnamed: L5.2, U2.42 (L2)
unnamed: L3.2, U2.38 (L3)
unnamed: L1.2, U2.13 (L4A)
unnamed: L1.1, U2.14 (L4B)
unnamed: C13.1, R3.2, R4.1, U2.16 (PFI)
unnamed: C214.1, R9.2, R10.1, U3.1 (REFIN)
unnamed: R36.1, R37.1, U4.13 (ADBUS0)
unnamed: R38.1, R39.1, U4.14 (ADBUS1)
unnamed: R35.1, U4.5 (REF)
unnamed: C38.1, U4.37 (VCCA)
unnamed: C36.1, U4.38 (VCCCORE)
unnamed: C40.1, C42.1, FB9.2, U4.3 (VPHY)
unnamed: C39.1, C41.1, FB8.2, U4.8 (VPLL)
unnamed: C34.1, U4.1 (XCSI), Y2.3
unnamed: C37.1, U4.2 (XCSO), Y2.1
unnamed: R51.1, U5.R10 (INIT_B_0)
unnamed: R50.1, S1.1, S1.3, U5.L6 (PROGRAM_B_0)
unnamed: R65.1, U5.D14 (PS_MIO40_501)
unnamed: R112.2, U5.L5 (PS_DDR_BA0_502)
unnamed: R111.2, U5.R4 (PS_DDR_BA1_502)
unnamed: R110.2, U5.J5 (PS_DDR_BA2_502)
unnamed: R114.2, U5.P5 (PS_DDR_CAS_B_502)
unnamed: R117.2, U5.N3 (PS_DDR_CKE_502)
unnamed: R115.2, U5.N1 (PS_DDR_CS_B_502)
unnamed: R113.2, U5.P4 (PS_DDR_RAS_B_502)
unnamed: R116.2, U5.M5 (PS_DDR_WE_B_502)
unnamed: R34.1, U6.48 (ISET)
unnamed: R21.2, U6.46 (XI)
unnamed: R121.1, U8.L8 (ZQ)
unnamed: R123.1, U9.L8 (ZQ)
unnamed: R122.1, U11.L8 (ZQ)
unnamed: C187.1, R124.2, R125.1, U12.1 (REFIN)
unnamed: R134.1, U13.6 (SCK)
unnamed: R131.2, U14.M6 (CLK)
unnamed: U14.A11 (DVDD), U14.G14 (DVDD), U14.M2 (DVDD), U14.P11 (DVDD)
unnamed: U14.A8 (DVDDQ), U14.B13 (DVDDQ), U14.C14 (DVDDQ), U14.G3 (DVDDQ), U14.G13 (DVDDQ), U14.H1 (DVDDQ), U14.H13 (DVDDQ), U14.M14 (DVDDQ), U14.N13 (DVDDQ), U14.P7 (DVDDQ), U14.P8 (DVDDQ)
unnamed: U14.A10 (DVSS), U14.C1 (DVSS), U14.H14 (DVSS), U14.K2 (DVSS), U14.M1 (DVSS)
unnamed: U14.A9 (DVSSQ), U14.A12 (DVSSQ), U14.D14 (DVSSQ), U14.F14 (DVSSQ), U14.L14 (DVSSQ), U14.N6 (DVSSQ), U14.P9 (DVSSQ), U14.P12 (DVSSQ)
unnamed: U14.A1 (NC), U14.A2 (NC), U14.A13 (NC), U14.A14 (NC), U14.B1 (NC), U14.B7 (NC), U14.B8 (NC), U14.B9 (NC), U14.B10 (NC), U14.B11 (NC), U14.B12 (NC), U14.B14 (NC), U14.C3 (NC), U14.C5 (NC), U14.C7 (NC), U14.C8 (NC), U14.C9 (NC), U14.C10 (NC), U14.C11 (NC), U14.C12 (NC), U14.C13 (NC), U14.D1 (NC), U14.D2 (NC), U14.D3 (NC), U14.D4 (NC), U14.D12 (NC), U14.D13 (NC), U14.E1 (NC), U14.E2 (NC), U14.E3 (NC), U14.E12 (NC), U14.E13 (NC), U14.E14 (NC), U14.F2 (NC), U14.F3 (NC), U14.F12 (NC), U14.F13 (NC), U14.G1 (NC), U14.G2 (NC), U14.G12 (NC), U14.H2 (NC), U14.H3 (NC), U14.H12 (NC), U14.J1 (NC), U14.J2 (NC), U14.J3 (NC), U14.J12 (NC), U14.J13 (NC), U14.K1 (NC), U14.K3 (NC), U14.K12 (NC), U14.K13 (NC), U14.K14 (NC), U14.L1 (NC), U14.L2 (NC), U14.L3 (NC), U14.L12 (NC), U14.L13 (NC), U14.M3 (NC), U14.M7 (NC), U14.M8 (NC), U14.M9 (NC), U14.M10 (NC), U14.M11 (NC), U14.M12 (NC), U14.M13 (NC), U14.N1 (NC), U14.N3 (NC), U14.N7 (NC), U14.N8 (NC), U14.N9 (NC), U14.N11 (NC), U14.N12 (NC), U14.N14 (NC), U14.P1 (NC), U14.P2 (NC), U14.P13 (NC), U14.P14 (NC)
unnamed: U14.A7 (RFU), U14.E5 (RFU), U14.K6 (RFU), U14.K7 (RFU)
unnamed: C194.1, U14.C2 (VDDI)
unnamed: U14.E8 (VSF), U14.E9 (VSF), U14.E10 (VSF), U14.F10 (VSF), U14.G10 (VSF), U14.K10 (VSF), U14.P10 (VSF)
unnamed: R138.1, U16.1 (DO)
unnamed: R141.1, U17.24 (RBIAS)
unnamed: R144.1, U17.25 (XO)
unnamed: R21.1, Y3.3 (OUT)

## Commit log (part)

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2025-05-31 initial commit; significant progress;
2025-06-02 ddr progress; added more conns;
2025-06-09 ps progress; added ftdi; mezz pinout pedinging;
2025-06-28 some ddr routing progress; layerstack per pcbway standard options, review reqd; commit prior to ddr split;
2025-07-07 added starage, usb sch; more design progress in sch;
2025-07-27 routing changes; added mezzanine; added pl ram;
2025-08-06 updated sch pdf; routign progress;
2025-09-08 replaced pmic;
